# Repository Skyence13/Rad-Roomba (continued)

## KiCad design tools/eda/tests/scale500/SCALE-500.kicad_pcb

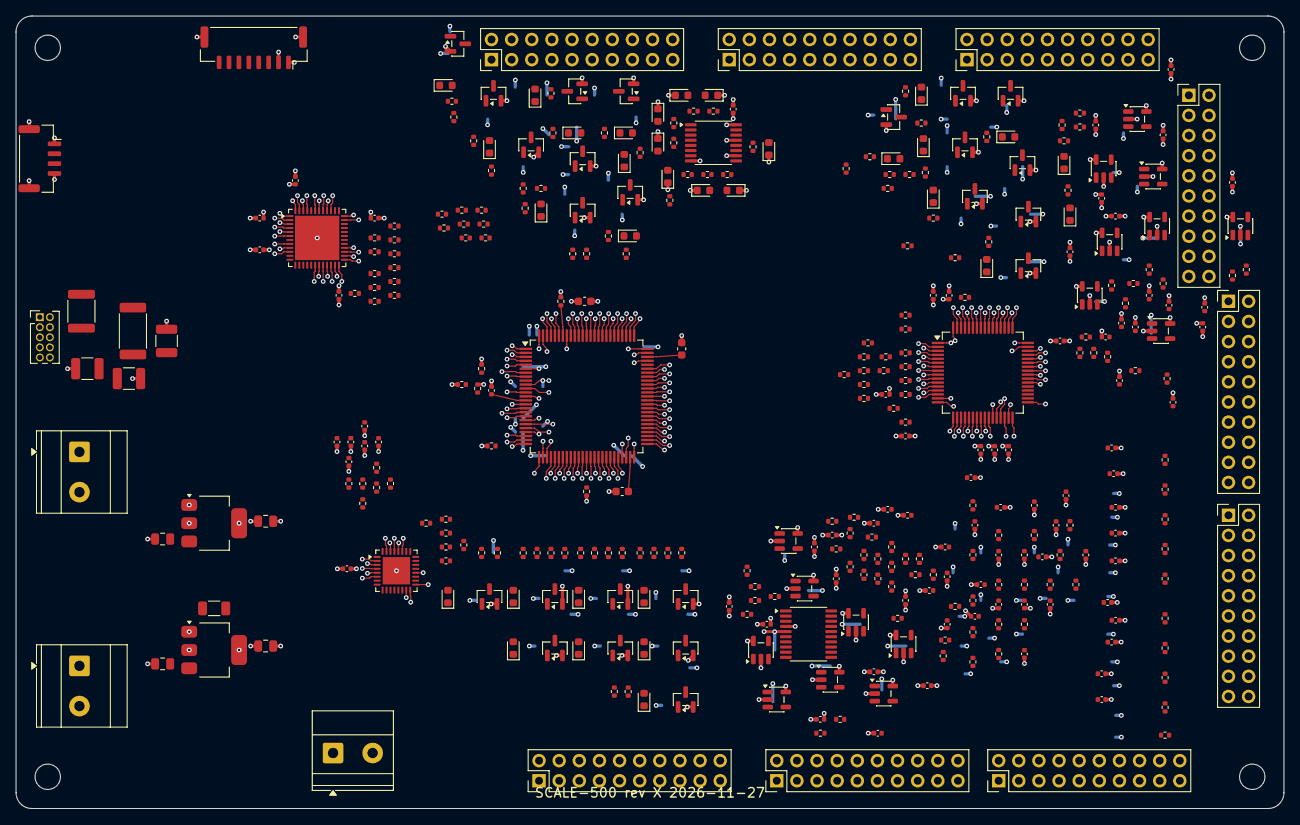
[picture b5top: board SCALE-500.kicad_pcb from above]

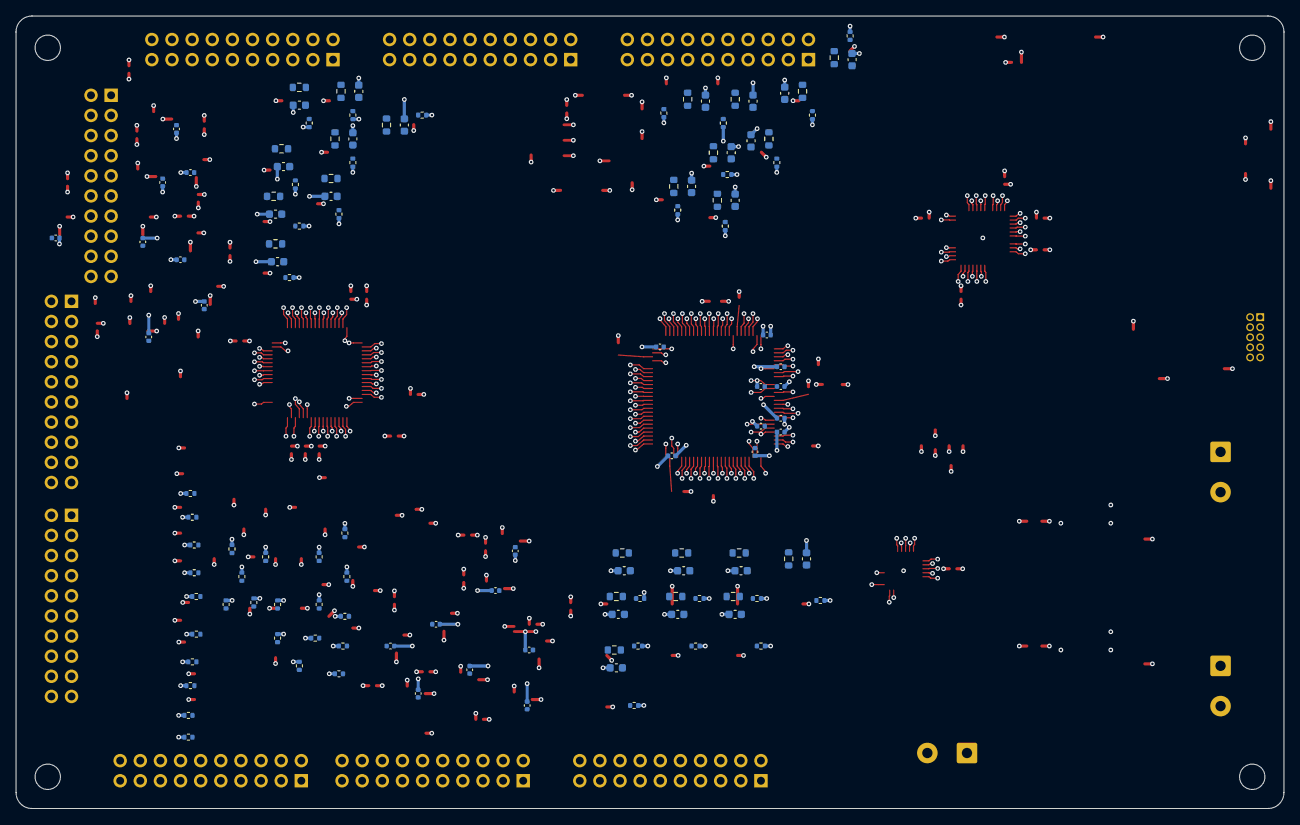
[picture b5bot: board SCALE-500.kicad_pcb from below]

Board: 6 copper layers, 160.0 x 100.0 mm, 497 parts (124 on the bottom side), 393 nets.

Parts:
C1, C2, C3: 22u; C_1210_3225Metric
C4, C6: 10u; C_0805_2012Metric
C5, C7: 22u; C_0805_2012Metric
C10, C11, C12, C13, C14, C15, C16, C17, C18, C19, C22, C30, C31, C32, C33, C34, C35, C36, C37, C40, C41, C42, C43, C44, C46, C47, C500, C501, C502, C503, C504, C505, C506, C507, C508, C509, C510, C511, C512, C513, C514, C515: 100n; C_0402_1005Metric
C20, C21: 2u2; C_0603_1608Metric
C23: 4u7; C_0603_1608Metric
C45: 1u; C_0402_1005Metric
C400, C401, C402, C403, C404, C405, C406, C407, C408, C409, C410, C411, C412, C413, C414, C415, C880, C881, C882, C883, C884, C885, C886, C887, C888, C889: 1n; C_0402_1005Metric
C600, C601, C602, C603, C604, C605, C606, C607, C608, C609, C610, C611, C612, C613, C614, C615: 100p; C_0402_1005Metric
C700, C701, C702, C703, C704, C705, C706, C707, C708, C709, C710, C711, C712, C713, C714, C715: 10n; C_0402_1005Metric
C860, C861, C862, C863, C864, C865: 47p; C_0402_1005Metric
C900, C901, C902, C903, C904, C905, C906, C907, C908, C909, C910, C911, C912, C913, C914, C915, C916, C917, C918, C919, C920, C921, C922, C923: 1n; C_0603_1608Metric
D200, D201, D202, D203, D204, D205, D206, D207: green; LED_0603_1608Metric
D300, D301, D302, D303, D304, D305, D306, D307, D308, D309, D310, D311, D312, D313, D314, D315, D316, D317, D318, D319, D320, D321, D322, D323: red; LED_0603_1608Metric
F1: 10A; Fuse_1812_4532Metric
H1, H2, H3, H4: M-hole 3.2mm; MountingHole_3.2mm_NPTH
J1: VBAT IN; TerminalBlock_Phoenix_MKDS-3-2-5.08_1x02_P5.08mm_Horizontal
J2: VBAT OUT A; TerminalBlock_Phoenix_MKDS-3-2-5.08_1x02_P5.08mm_Horizontal
J3: 12V IN; TerminalBlock_Phoenix_MKDS-1,5-2_1x02_P5.00mm_Horizontal
J10: OUT0; PinHeader_2x10_P2.54mm_Vertical
J11: OUT1; PinHeader_2x10_P2.54mm_Vertical
J12: OUT2; PinHeader_2x10_P2.54mm_Vertical
J20: AOUT0; PinHeader_2x10_P2.54mm_Vertical
J21: AOUT1; PinHeader_2x10_P2.54mm_Vertical
J30: AIN0; PinHeader_2x10_P2.54mm_Vertical
J31: AIN1; PinHeader_2x10_P2.54mm_Vertical
J32: DIN; PinHeader_2x10_P2.54mm_Vertical
J40: SWD; PinHeader_2x05_P1.27mm_Vertical
J41: GH8; JST_GH_SM08B-GHS-TB_1x08-1MP_P1.25mm_Horizontal
J42: GH4; JST_GH_SM04B-GHS-TB_1x04-1MP_P1.25mm_Horizontal
J43: EXP; PinHeader_2x10_P2.54mm_Vertical
Q300, Q301, Q302, Q303, Q304, Q305, Q306, Q307, Q308, Q309, Q310, Q311, Q312, Q313, Q314, Q315, Q316, Q317, Q318, Q319, Q320, Q321, Q322, Q323: AO3400A; SOT-23
R1: 0R; R_1206_3216Metric
R10, R11, R700, R701, R702, R703, R704, R705, R706, R707, R708, R709, R710, R711, R712, R713, R714, R715: 10k; R_0402_1005Metric
R12, R13, R14, R15: 4k7; R_0402_1005Metric
R100, R101, R102, R103, R104, R105, R106, R107, R108, R109, R110, R111, R112, R113, R114, R115, R800, R801, R802, R803, R804, R805, R806, R807, R808, R809, R810, R811, R820, R821, R822, R823, R824, R825, R830, R831, R832, R833, R840, R841, R842, R843, R844, R845, R846, R847, R850, R851, R852, R853, R854, R855, R856, R857, R860, R861, R862, R863, R864, R865: 33R; R_0402_1005Metric
R200, R201, R202, R203, R204, R205, R206, R207, R400, R401, R402, R403, R404, R405, R406, R407, R408, R409, R410, R411, R412, R413, R414, R415, R870, R871, R872, R873, R874, R875, R876, R877, R878, R879: 1k; R_0402_1005Metric
R300, R301, R302, R303, R304, R305, R306, R307, R308, R309, R310, R311, R312, R313, R314, R315, R316, R317, R318, R319, R320, R321, R322, R323, R500, R501, R502, R503, R504, R505, R506, R507, R508, R509, R510, R511, R512, R513, R514, R515: 100R; R_0402_1005Metric
R330, R331, R332, R333, R334, R335, R336, R337, R338, R339, R340, R341, R342, R343, R344, R345, R346, R347, R348, R349, R350, R351, R352, R353, R730, R731, R732, R733, R734, R735, R736, R737, R738, R739, R740, R741, R742, R743, R744, R745, R880, R881, R882, R883, R884, R885, R886, R887, R888, R889: 100k; R_0402_1005Metric
R360, R361, R362, R363, R364, R365, R366, R367, R368, R369, R370, R371, R372, R373, R374, R375, R376, R377, R378, R379, R380, R381, R382, R383: 2k2; R_0402_1005Metric
R900, R901, R902, R903, R904, R905, R906, R907, R908, R909, R910, R911, R912, R913, R914, R915, R916, R917, R918, R919, R920, R921, R922, R923: 47R; R_0603_1608Metric
RS1: 2m; R_2512_6332Metric
U1: STM32F407VET6; LQFP-100_14x14mm_P0.5mm
U2: STM32G474RET6; LQFP-64_10x10mm_P0.5mm
U3: STM32F103CBU6; QFN-48-1EP_7x7mm_P0.5mm_EP5.6x5.6mm
U4: STM32G031K8U6; QFN-32-1EP_5x5mm_P0.5mm_EP3.45x3.45mm
U5: STM32G031F8P6; TSSOP-20_4.4x6.5mm_P0.65mm
U6: 74HC595; TSSOP-16_4.4x5mm_P0.65mm
U7: AMS1117-5.0; SOT-223-3_TabPin2
U8: AMS1117-3.3; SOT-223-3_TabPin2
U400, U401, U402, U403, U404, U405, U406, U407, U408, U409, U410, U411, U412, U413, U414, U415: MCP6001; SOT-23-5

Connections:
+3V3: C7.1, C10.1, C11.1, C12.1, C13.1, C14.1, C15.1, C16.1, C17.1, C18.1, C19.1, C23.1, C30.1, C31.1, C32.1, C33.1, C34.1, C35.1, C36.1, C37.1, C40.1, C41.1, C42.1, C43.1, C44.1, C45.1, C46.1, C47.1, C500.1, C501.1, C502.1, C503.1, C504.1, C505.1, C506.1, C507.1, C508.1, C509.1, C510.1, C511.1, C512.1, C513.1, C514.1, C515.1, J20.19, J21.19, J40.1, J41.1, J42.1, J43.19, R10.1, R12.1, R13.1, R14.1, R15.1, U1.6, U1.11, U1.19, U1.21, U1.22, U1.28, U1.50, U1.75, U1.100, U2.1, U2.16, U2.28, U2.29, U2.32, U2.48, U2.64, U3.1, U3.9, U3.24, U3.36, U3.48, U4.4, U5.4, U6.10, U6.16, U8.2, U400.5, U401.5, U402.5, U403.5, U404.5, U405.5, U406.5, U407.5, U408.5, U409.5, U410.5, U411.5, U412.5, U413.5, U414.5, U415.5
+5V: C5.1, C6.1, J20.20, J21.20, J43.20, U7.2, U8.3
+12V: C4.1, J3.1, J10.2, J10.4, J10.6, J10.8, J10.10, J10.12, J10.14, J10.16, J11.2, J11.4, J11.6, J11.8, J11.10, J11.12, J11.14, J11.16, J12.2, J12.4, J12.6, J12.8, J12.10, J12.12, J12.14, J12.16, R1.1, U7.3
AIN00: C700.1, R700.2, U2.54
AIN01: C701.1, R701.2, U2.2
AIN02: C702.1, R702.2, U2.3
AIN03: C703.1, R703.2, U2.4
AIN04: C704.1, R704.2, U2.12
AIN05: C705.1, R705.2, U2.13
AIN06: C706.1, R706.2, U2.14
AIN07: C707.1, R707.2, U2.17
AIN08: C708.1, R708.2, U2.18
AIN09: C709.1, R709.2, U2.19
AIN10: C710.1, R710.2, U2.20
AIN11: C711.1, R711.2, U2.21
AIN12: C712.1, R712.2, U2.42
AIN13: C713.1, R713.2, U2.43
AIN14: C714.1, R714.2, U2.44
AIN15: C715.1, R715.2, U2.45
AIN_X00: J30.1, R700.1, R730.1
AIN_X01: J30.2, R701.1, R731.1
AIN_X02: J30.3, R702.1, R732.1
AIN_X03: J30.4, R703.1, R733.1
AIN_X04: J30.5, R704.1, R734.1
AIN_X05: J30.6, R705.1, R735.1
AIN_X06: J30.7, R706.1, R736.1
AIN_X07: J30.8, R707.1, R737.1
AIN_X08: J31.1, R708.1, R738.1
AIN_X09: J31.2, R709.1, R739.1
AIN_X10: J31.3, R710.1, R740.1
AIN_X11: J31.4, R711.1, R741.1
AIN_X12: J31.5, R712.1, R742.1
AIN_X13: J31.6, R713.1, R743.1
AIN_X14: J31.7, R714.1, R744.1
AIN_X15: J31.8, R715.1, R745.1
AO00: C600.1, J20.1, R500.2
AO01: C601.1, J20.3, R501.2
AO02: C602.1, J20.5, R502.2
AO03: C603.1, J20.7, R503.2
AO04: C604.1, J20.9, R504.2
AO05: C605.1, J20.11, R505.2
AO06: C606.1, J20.13, R506.2
AO07: C607.1, J20.15, R507.2
AO08: C608.1, J21.1, R508.2
AO09: C609.1, J21.3, R509.2
AO10: C610.1, J21.5, R510.2
AO11: C611.1, J21.7, R511.2
AO12: C612.1, J21.9, R512.2
AO13: C613.1, J21.11, R513.2
AO14: C614.1, J21.13, R514.2
AO15: C615.1, J21.15, R515.2
AUXH00: R840.1, U3.43
AUXH01: R841.1, U3.45
AUXH02: R842.1, U3.46
AUXH03: R843.1, U3.21
AUXH04: R844.1, U3.22
AUXH05: R845.1, U3.25
AUXH06: R846.1, U3.26
AUXH07: R847.1, U3.27
AUXHC00: J43.1, R840.2
AUXHC01: J43.2, R841.2
AUXHC02: J43.3, R842.2
AUXHC03: J43.4, R843.2
AUXHC04: J43.5, R844.2
AUXHC05: J43.6, R845.2
AUXHC06: J43.7, R846.2
AUXHC07: J43.8, R847.2
AUXT00: R850.1, U5.2
AUXT01: R851.1, U5.7
AUXT02: R852.1, U5.8
AUXT03: R853.1, U5.9
AUXT04: R854.1, U5.10
AUXT05: R855.1, U5.11
AUXT06: R856.1, U5.12
AUXT07: R857.1, U5.13
AUXTC00: J43.9, R850.2
AUXTC01: J43.10, R851.2
AUXTC02: J43.11, R852.2
AUXTC03: J43.12, R853.2
AUXTC04: J43.13, R854.2
AUXTC05: J43.14, R855.2
AUXTC06: J43.15, R856.2
AUXTC07: J43.16, R857.2
B2R_00: R100.2, U2.7
B2R_01: R101.2, U2.5
B2R_02: R102.2, U2.6
B2R_03: R103.2, U2.55
B2R_04: R104.2, U2.8
B2R_05: R105.2, U2.9
B2R_06: R106.2, U2.10
B2R_07: R107.2, U2.11
B2R_08: R108.2, U2.22
B2R_09: R109.2, U2.23
B2R_10: R110.2, U2.38
B2R_11: R111.2, U2.39
B2R_12: R112.2, U2.40
B2R_13: R113.2, U2.41
B2R_14: R114.2, U2.52
B2R_15: R115.2, U2.53
B2_00: R100.1, U1.12
B2_01: R101.1, U1.13
B2_02: R102.1, U1.97
B2_03: R103.1, U1.98
B2_04: R104.1, U1.1
B2_05: R105.1, U1.2
B2_06: R106.1, U1.3
B2_07: R107.1, U1.4
B2_08: R108.1, U1.5
B2_09: R109.1, U1.38
B2_10: R110.1, U1.39
B2_11: R111.1, U1.40
B2_12: R112.1, U1.41
B2_13: R113.1, U1.42
B2_14: R114.1, U1.43
B2_15: R115.1, U1.44
B3R_00: R800.2, U3.5
B3R_01: R801.2, U3.6
B3R_02: R802.2, U3.2
B3R_03: R803.2, U3.3
B3R_04: R804.2, U3.4
B3R_05: R805.2, U3.18
B3R_06: R806.2, U3.19
B3R_07: R807.2, U3.20
B3R_08: R808.2, U3.39
B3R_09: R809.2, U3.40
B3R_10: R810.2, U3.41
B3R_11: R811.2, U3.42
B3_00: R800.1, U1.45
B3_01: R801.1, U1.46
B3_02: R802.1, U1.81
B3_03: R803.1, U1.82
B3_04: R804.1, U1.83
B3_05: R805.1, U1.84
B3_06: R806.1, U1.85
B3_07: R807.1, U1.86
B3_08: R808.1, U1.87
B3_09: R809.1, U1.88
B3_10: R810.1, U1.55
B3_11: R811.1, U1.56
B4R_00: R820.2, U4.6
B4R_01: R821.2, U4.20
B4R_02: R822.2, U4.2
B4R_03: R823.2, U4.3
B4R_04: R824.2, U4.15
B4R_05: R825.2, U4.16
B4_00: R820.1, U1.57
B4_01: R821.1, U1.58
B4_02: R822.1, U1.59
B4_03: R823.1, U1.60
B4_04: R824.1, U1.61
B4_05: R825.1, U1.62
B5R_00: R830.2, U5.6
B5R_01: R831.2, U5.3
B5R_02: R832.2, U5.20
B5R_03: R833.2, U5.1
B5_00: R830.1, U1.23
B5_01: R831.1, U1.24
B5_02: R832.1, U1.25
B5_03: R833.1, U1.26
BOOT0: R11.1, U1.94
DIN00: C880.1, R870.2, U1.34
DIN01: C881.1, R871.2, U1.63
DIN02: C882.1, R872.2, U1.64
DIN03: C883.1, R873.2, U1.65
DIN04: C884.1, R874.2, U1.66
DIN05: C885.1, R875.2, U1.78
DIN06: C886.1, R876.2, U1.79
DIN07: C887.1, R877.2, U1.80
DIN08: C888.1, R878.2, U1.7
DIN09: C889.1, R879.2, U1.8
DIN_X00: J32.1, R870.1, R880.1
DIN_X01: J32.2, R871.1, R881.1
DIN_X02: J32.3, R872.1, R882.1
DIN_X03: J32.4, R873.1, R883.1
DIN_X04: J32.5, R874.1, R884.1
DIN_X05: J32.6, R875.1, R885.1
DIN_X06: J32.7, R876.1, R886.1
DIN_X07: J32.8, R877.1, R887.1
DIN_X08: J32.9, R878.1, R888.1
DIN_X09: J32.10, R879.1, R889.1
FET_IN00: R300.1, U1.32
FET_IN01: R301.1, U1.67
FET_IN02: R302.1, U1.68
FET_IN03: R303.1, U1.69
FET_IN04: R304.1, U1.70
FET_IN05: R305.1, U1.71
FET_IN06: R306.1, U1.72
FET_IN07: R307.1, U1.76
FET_IN08: R308.1, U1.77
FET_IN09: R309.1, U1.35
FET_IN10: R310.1, U1.36
FET_IN11: R311.1, U1.37
FET_IN12: R312.1, U1.89
FET_IN13: R313.1, U1.90
FET_IN14: R314.1, U1.91
FET_IN15: R315.1, U1.92
FET_IN16: R316.1, U1.93
FET_IN17: R317.1, U1.95
FET_IN18: R318.1, U1.96
FET_IN19: R319.1, U1.47
FET_IN20: R320.1, U1.48
FET_IN21: R321.1, U1.51
FET_IN22: R322.1, U1.52
FET_IN23: R323.1, U1.53
G00: Q300.1, R300.2, R330.1
G01: Q301.1, R301.2, R331.1
G02: Q302.1, R302.2, R332.1
G03: Q303.1, R303.2, R333.1
G04: Q304.1, R304.2, R334.1
G05: Q305.1, R305.2, R335.1
G06: Q306.1, R306.2, R336.1
G07: Q307.1, R307.2, R337.1
G08: Q308.1, R308.2, R338.1
G09: Q309.1, R309.2, R339.1
G10: Q310.1, R310.2, R340.1
G11: Q311.1, R311.2, R341.1
G12: Q312.1, R312.2, R342.1
G13: Q313.1, R313.2, R343.1
G14: Q314.1, R314.2, R344.1
G15: Q315.1, R315.2, R345.1
G16: Q316.1, R316.2, R346.1
G17: Q317.1, R317.2, R347.1
G18: Q318.1, R318.2, R348.1
G19: Q319.1, R319.2, R349.1
G20: Q320.1, R320.2, R350.1
G21: Q321.1, R321.2, R351.1
G22: Q322.1, R322.2, R352.1
G23: Q323.1, R323.2, R353.1
GH0: R860.1, U4.17
GH1: R861.1, U4.27
GH2: R862.1, U4.28
GH3: R863.1, U4.29
GH4: R864.1, U4.30
GH5: R865.1, U4.31
GHC0: C860.1, J41.3, R860.2
GHC1: C861.1, J41.4, R861.2
GHC2: C862.1, J41.5, R862.2
GHC3: C863.1, J41.6, R863.2
GHC4: C864.1, J41.7, R864.2
GHC5: C865.1, J41.8, R865.2
GND: C1.2, C2.2, C3.2, C4.2, C5.2, C6.2, C7.2, C10.2, C11.2, C12.2, C13.2, C14.2, C15.2, C16.2, C17.2, C18.2, C19.2, C20.2, C21.2, C22.2, C23.2, C30.2, C31.2, C32.2, C33.2, C34.2, C35.2, C36.2, C37.2, C40.2, C41.2, C42.2, C43.2, C44.2, C45.2, C46.2, C47.2, C400.2, C401.2, C402.2, C403.2, C404.2, C405.2, C406.2, C407.2, C408.2, C409.2, C410.2, C411.2, C412.2, C413.2, C414.2, C415.2, C500.2, C501.2, C502.2, C503.2, C504.2, C505.2, C506.2, C507.2, C508.2, C509.2, C510.2, C511.2, C512.2, C513.2, C514.2, C515.2, C600.2, C601.2, C602.2, C603.2, C604.2, C605.2, C606.2, C607.2, C608.2, C609.2, C610.2, C611.2, C612.2, C613.2, C614.2, C615.2, C700.2, C701.2, C702.2, C703.2, C704.2, C705.2, C706.2, C707.2, C708.2, C709.2, C710.2, C711.2, C712.2, C713.2, C714.2, C715.2, C860.2, C861.2, C862.2, C863.2, C864.2, C865.2, C880.2, C881.2, C882.2, C883.2, C884.2, C885.2, C886.2, C887.2, C888.2, C889.2, C900.2, C901.2, C902.2, C903.2, C904.2, C905.2, C906.2, C907.2, C908.2, C909.2, C910.2, C911.2, C912.2, C913.2, C914.2, C915.2, C916.2, C917.2, C918.2, C919.2, C920.2, C921.2, C922.2, C923.2, D200.1, D201.1, D202.1, D203.1, D204.1, D205.1, D206.1, D207.1, J1.2, J2.2, J3.2, J10.17, J10.18, J10.19, J10.20, J11.17, J11.18, J11.19, J11.20, J12.17, J12.18, J12.19, J12.20, J20.2, J20.4, J20.6, J20.8, J20.10, J20.12, J20.14, J20.16, J20.17, J20.18, J21.2, J21.4, J21.6, J21.8, J21.10, J21.12, J21.14, J21.16, J21.17, J21.18, J30.9, J30.10, J30.11, J30.12, J30.13, J30.14, J30.15, J30.16, J30.17, J30.18, J30.19, J30.20, J31.9, J31.10, J31.11, J31.12, J31.13, J31.14, J31.15, J31.16, J31.17, J31.18, J31.19, J31.20, J32.11, J32.12, J32.13, J32.14, J32.15, J32.16, J32.17, J32.18, J32.19, J32.20, J40.3, J40.5, J40.7, J40.9, J41.2, J41.MP, J42.4, J42.MP, J43.17, J43.18, Q300.2, Q301.2, Q302.2, Q303.2, Q304.2, Q305.2, Q306.2, Q307.2, Q308.2, Q309.2, Q310.2, Q311.2, Q312.2, Q313.2, Q314.2, Q315.2, Q316.2, Q317.2, Q318.2, Q319.2, Q320.2, Q321.2, Q322.2, Q323.2, R11.2, R330.2, R331.2, R332.2, R333.2, R334.2, R335.2, R336.2, R337.2, R338.2, R339.2, R340.2, R341.2, R342.2, R343.2, R344.2, R345.2, R346.2, R347.2, R348.2, R349.2, R350.2, R351.2, R352.2, R353.2, R730.2, R731.2, R732.2, R733.2, R734.2, R735.2, R736.2, R737.2, R738.2, R739.2, R740.2, R741.2, R742.2, R743.2, R744.2, R745.2, R880.2, R881.2, R882.2, R883.2, R884.2, R885.2, R886.2, R887.2, R888.2, R889.2, U1.10, U1.20, U1.27, U1.74, U1.99, U2.15, U2.27, U2.31, U2.47, U2.63, U3.8, U3.23, U3.35, U3.47, U3.49, U4.5, U4.33, U5.5, U6.8, U6.13, U7.1, U8.1, U400.2, U401.2, U402.2, U403.2, U404.2, U405.2, U406.2, U407.2, U408.2, U409.2, U410.2, U411.2, U412.2, U413.2, U414.2, U415.2
I2C_SCL: J42.2, R12.2, U1.16, U3.28
I2C_SDA: J42.3, R13.2, U1.17, U3.10
LK00: D300.1, R360.1
LK01: D301.1, R361.1
LK02: D302.1, R362.1
LK03: D303.1, R363.1
LK04: D304.1, R364.1
LK05: D305.1, R365.1
LK06: D306.1, R366.1
LK07: D307.1, R367.1
LK08: D308.1, R368.1
LK09: D309.1, R369.1
LK10: D310.1, R370.1
LK11: D311.1, R371.1
LK12: D312.1, R372.1
LK13: D313.1, R373.1
LK14: D314.1, R374.1
LK15: D315.1, R375.1
LK16: D316.1, R376.1
LK17: D317.1, R377.1
LK18: D318.1, R378.1
LK19: D319.1, R379.1
LK20: D320.1, R380.1
LK21: D321.1, R381.1
LK22: D322.1, R382.1
LK23: D323.1, R383.1
NRST: C22.1, J40.6, R10.2, U1.14
OPB00: C400.1, R400.2, U400.3
OPB01: C401.1, R401.2, U401.3
OPB02: C402.1, R402.2, U402.3
OPB03: C403.1, R403.2, U403.3
OPB04: C404.1, R404.2, U404.3
OPB05: C405.1, R405.2, U405.3
OPB06: C406.1, R406.2, U406.3
OPB07: C407.1, R407.2, U407.3
OPB08: C408.1, R408.2, U408.3
OPB09: C409.1, R409.2, U409.3
OPB10: C410.1, R410.2, U410.3
OPB11: C411.1, R411.2, U411.3
OPB12: C412.1, R412.2, U412.3
OPB13: C413.1, R413.2, U413.3
OPB14: C414.1, R414.2, U414.3
OPB15: C415.1, R415.2, U415.3
OPIN00: R400.1, U2.46
OPIN01: R401.1, U2.49
OPIN02: R402.1, U2.50
OPIN03: R403.1, U2.51
OPIN04: R404.1, U2.24
OPIN05: R405.1, U2.25
OPIN06: R406.1, U2.26
OPIN07: R407.1, U2.56
OPIN08: R408.1, U2.57
OPIN09: R409.1, U2.58
OPIN10: R410.1, U2.59
OPIN11: R411.1, U2.60
OPIN12: R412.1, U2.61
OPIN13: R413.1, U2.62
OPIN14: R414.1, U2.30
OPIN15: R415.1, U2.33
OPO00: R500.1, U400.1, U400.4
OPO01: R501.1, U401.1, U401.4
OPO02: R502.1, U402.1, U402.4
OPO03: R503.1, U403.1, U403.4
OPO04: R504.1, U404.1, U404.4
OPO05: R505.1, U405.1, U405.4
OPO06: R506.1, U406.1, U406.4
OPO07: R507.1, U407.1, U407.4
OPO08: R508.1, U408.1, U408.4
OPO09: R509.1, U409.1, U409.4
OPO10: R510.1, U410.1, U410.4
OPO11: R511.1, U411.1, U411.4
OPO12: R512.1, U412.1, U412.4
OPO13: R513.1, U413.1, U413.4
OPO14: R514.1, U414.1, U414.4
OPO15: R515.1, U415.1, U415.4
SN00: C900.1, R900.2
SN01: C901.1, R901.2
SN02: C902.1, R902.2
SN03: C903.1, R903.2
SN04: C904.1, R904.2
SN05: C905.1, R905.2
SN06: C906.1, R906.2
SN07: C907.1, R907.2
SN08: C908.1, R908.2
SN09: C909.1, R909.2
SN10: C910.1, R910.2
SN11: C911.1, R911.2
SN12: C912.1, R912.2
SN13: C913.1, R913.2
SN14: C914.1, R914.2
SN15: C915.1, R915.2
SN16: C916.1, R916.2
SN17: C917.1, R917.2
SN18: C918.1, R918.2
SN19: C919.1, R919.2
SN20: C920.1, R920.2
SN21: C921.1, R921.2
SN22: C922.1, R922.2
SN23: C923.1, R923.2
SRL0: D200.2, R200.2
SRL1: D201.2, R201.2
SRL2: D202.2, R202.2
SRL3: D203.2, R203.2
SRL4: D204.2, R204.2
SRL5: D205.2, R205.2
SRL6: D206.2, R206.2
SRL7: D207.2, R207.2
SRQ0: R200.1, U6.15
SRQ1: R201.1, U6.1
SRQ2: R202.1, U6.2
SRQ3: R203.1, U6.3
SRQ4: R204.1, U6.4
SRQ5: R205.1, U6.5
SRQ6: R206.1, U6.6
SRQ7: R207.1, U6.7
SR_CLK: U1.30, U6.11
SR_LAT: U1.31, U6.12
SR_SER: U1.29, U6.14
SW00: J10.1, Q300.3, R360.2, R900.1
SW01: J10.3, Q301.3, R361.2, R901.1
SW02: J10.5, Q302.3, R362.2, R902.1
SW03: J10.7, Q303.3, R363.2, R903.1
SW04: J10.9, Q304.3, R364.2, R904.1
SW05: J10.11, Q305.3, R365.2, R905.1
SW06: J10.13, Q306.3, R366.2, R906.1
SW07: J10.15, Q307.3, R367.2, R907.1
SW08: J11.1, Q308.3, R368.2, R908.1
SW09: J11.3, Q309.3, R369.2, R909.1
SW10: J11.5, Q310.3, R370.2, R910.1
SW11: J11.7, Q311.3, R371.2, R911.1
SW12: J11.9, Q312.3, R372.2, R912.1
SW13: J11.11, Q313.3, R373.2, R913.1
SW14: J11.13, Q314.3, R374.2, R914.1
SW15: J11.15, Q315.3, R375.2, R915.1
SW16: J12.1, Q316.3, R376.2, R916.1
SW17: J12.3, Q317.3, R377.2, R917.1
SW18: J12.5, Q318.3, R378.2, R918.1
SW19: J12.7, Q319.3, R379.2, R919.1
SW20: J12.9, Q320.3, R380.2, R920.1
SW21: J12.11, Q321.3, R381.2, R921.1
SW22: J12.13, Q322.3, R382.2, R922.1
SW23: J12.15, Q323.3, R383.2, R923.1
SWCLK: J40.4, U1.15
SWDIO: J40.2, R15.2, U1.54
UART_RX: J40.10, R14.2, U1.33
UART_TX: J40.8, U1.18
VBAT: F1.1, J1.1
VBAT_F: F1.2, RS1.1
VBAT_S: C1.1, C2.1, C3.1, J2.1, RS1.2
VCAP1: C20.1, U1.49
VCAP2: C21.1, U1.73
VLED: D300.2, D301.2, D302.2, D303.2, D304.2, D305.2, D306.2, D307.2, D308.2, D309.2, D310.2, D311.2, D312.2, D313.2, D314.2, D315.2, D316.2, D317.2, D318.2, D319.2, D320.2, D321.2, D322.2, D323.2, R1.2

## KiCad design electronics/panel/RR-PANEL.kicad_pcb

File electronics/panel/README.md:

# RR-PANEL rev A — annunciator panel (stage 2, KiCad 9)

| | |
|---|---|
| Netlist source | `design/circuit.py` (stage 1, reviewed baseline — not edited) |
| Board definition | `board.py` (the only hand-edited file; everything else is generated) |
| Board | 70 × 24 mm, 2 layers, 1.6 mm, 24 parts (19 fitted + 2 holes, 2 fiducials, 3 test pads), 15 nets |
| Result | **PASS** — ERC 0 errors / 0 warnings, DRC 0 errors / 0 warnings, 0 unconnected, schematic parity 0, netlist cross-check OK (24 components, 15 nets) |

## Commands

```
python3 electronics/panel/design/circuit.py                 # stage-1 self-check
python3 tools/eda/rrkicad.py build electronics/panel/board.py   # schematic, PCB, route (cached SES), ERC, DRC, all outputs (~25 s)
python3 tools/eda/rrkicad.py build electronics/panel/board.py --reroute   # force a fresh Freerouting run (~15 s routing)
python3 tools/eda/rrkicad.py check electronics/panel/board.py   # re-run ERC/DRC on the existing files
```

Outputs (`out/`): `RR-PANEL-schematic.pdf`, `gerber/` (Gerbers, PTH/NPTH Excellon, drill maps, job file),
`RR-PANEL-pos.csv`, `RR-PANEL-bom.csv`, `RR-PANEL-fab.pdf`, `RR-PANEL-assembly-top.pdf` / `-bottom.pdf`,
`RR-PANEL-copper.pdf`, `RR-PANEL.step`, `RR-PANEL-render-top.png` / `-bottom.png`, `pinmap.json`, `RR-PANEL.net`.
Reports: `reports/summary.json` (status, counts, BOM verify list), `reports/erc.*`, `reports/drc.*`,
`reports/import_report.json` (importer: 24 stock symbols, 0 local, 0 rejected hints, 0 missing footprints).
The routing result is `route/RR-PANEL.ses` + `route/route_meta.json` (keep under version control: the build re-uses it).

## Frame mapping

`circuit.py` / envelope board frame (u, v) → tool board frame (X, Y) = (u, v), no rotation, no offset.
Origin = lower-left corner seen from the top (component) side; X along the 70 mm axis in the LED order
READY (u 9) … FAULT (u 61); Y along the 24 mm axis. Pick-and-place, `pinmap.json`, the STEP model and
the drill origin use this frame. The board's orientation in the robot (`board_envelopes.yaml` RR-PANEL:
long axis along base y, component side up) does not say which end of u points to +y: **mechanical to
confirm** which edge the J1 cable leaves over (see below).

## What is tool-checked

ERC (0/0), DRC with schematic parity (0/0, 0 unconnected), pin-by-pin netlist cross-check of the generated
schematic against the definition (which is `circuit.py` imported 1:1), courtyards, edge clearance, hole
keep-outs (6 mm copper keep-out around H1/H2). **Not** checked by a tool: light-pipe alignment, the
mechanical fit in the shell, LED brightness, sounder level.

## Deviations from stage 1 (placement only — no net or part changes)

| # | What | Why |
|---|---|---|
| P1 | J1 and J2 are on the **top** side (stage 1: bottom side), at (30, 20.6) and (49.5, 20.6), mating face towards the v = 24 edge; the cable leaves over that long edge, not along the long axis | Envelope: bottom 3 mm max, GH side-entry header 4.25 mm. CCR-E08(d) offered "allow 4.5 mm or move them to the top"; no 4.5 mm allowance was granted (`board_envelopes.yaml` still says 3 mm), top allows 8 mm. A 10-pin GH (17 mm with pegs) cannot face a short edge: with H2's keep-out only 16 mm of the 24 mm edge is free. `harness/cables.md` W-023 / `harness/connectors.yaml` PNL.J1 still say "bottom side" — harness to update. |
| P2 | Holes, fiducials and test pads (`(pcb feature)` MPN) are excluded from the BOM | The stock footprints carry "exclude from BOM"; matching the symbol avoids a parity mismatch. They remain in the schematic and the PCB. |
| P3 | Silkscreen legend per LED (READY, MOVING, HOLD, CHARGE, FAULT) next to each LED on the top side | Assembly/service aid only. |

## Open items / UNVERIFIED

* `verify=True` from stage 1 (BOM notes): LED1–LED5 (Würth MPNs, intensity through the light pipe), BZ1 (Murata PKLCS1212E data recalled; sound level probably too low — fit the external sounder on J2).
* Mounting-hole positions (3.5, 20.5) / (66.5, 20.5) are the stage-1 proposal; mechanical gave none.
* Cable exit over the v = 24 edge (P1) and which board end faces +y in the robot: mechanical/harness to confirm.
* JST GH −25 °C rating (CCR-E05) unchanged.
* Only two top-side fiducials (as in `circuit.py`); the bottom side has no fiducials — acceptable for 0603/0805/SOD-123 and the 12 mm buzzer, add two if the assembler asks.

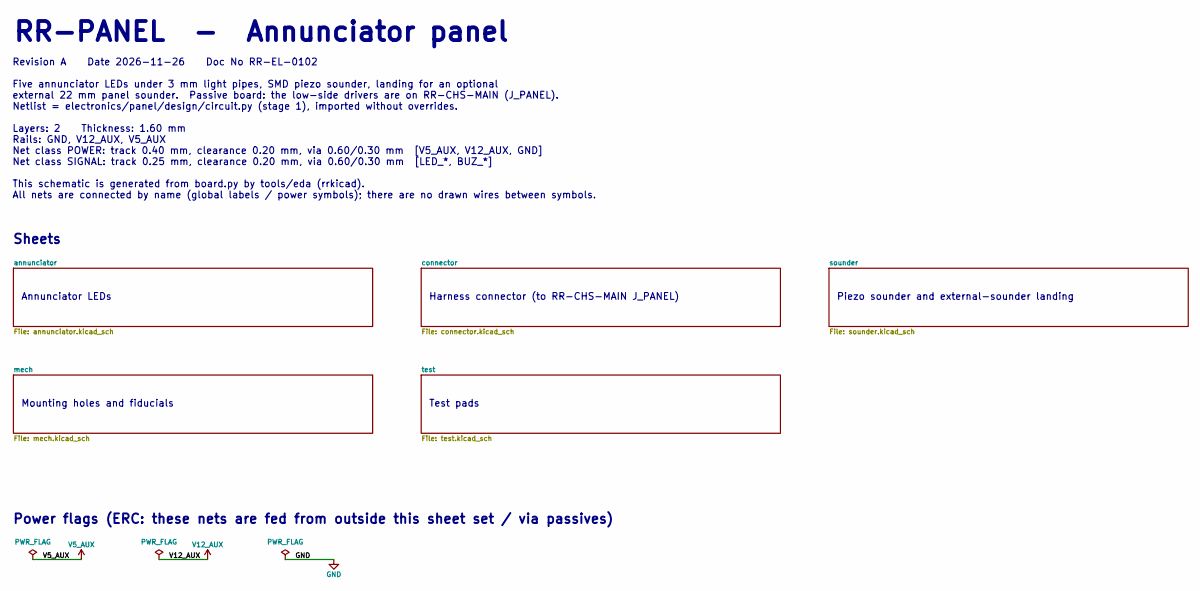
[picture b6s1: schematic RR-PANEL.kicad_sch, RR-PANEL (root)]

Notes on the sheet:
RR-PANEL - Annunciator panel
Revision A Date 2026-11-26 Doc No RR-EL-0102 Five annunciator LEDs under 3 mm light pipes, SMD piezo sounder, landing for an optional external 22 mm panel sounder. Passive board: the low-side drivers are on RR-CHS-MAIN (J_PANEL). Netlist = electronics/panel/design/circuit.py (stage 1), imported wit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
Sheets
Annunciator LEDs
Harness connector (to RR-CHS-MAIN J_PANEL)
Piezo sounder and external-sounder landing
Mounting holes and fiducials
Test pads
Power flags (ERC: these nets are fed from outside this sheet set / via passives)

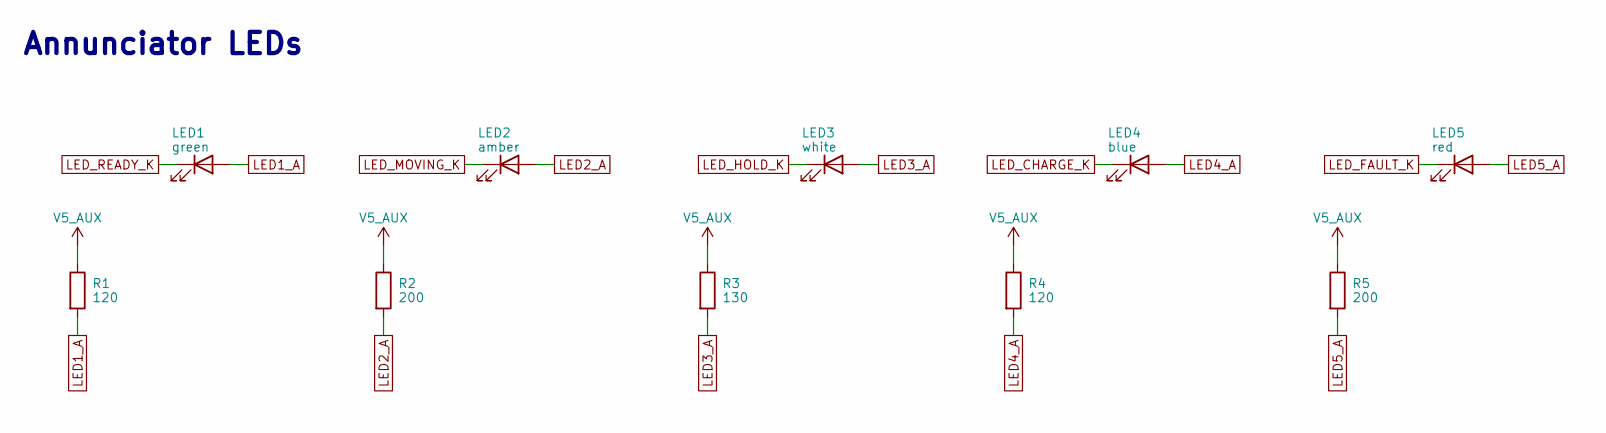
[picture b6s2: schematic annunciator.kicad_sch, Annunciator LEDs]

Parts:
LED1: green; LED_0805_2012Metric; MPN 150080GS75000
LED2: amber; LED_0805_2012Metric; MPN 150080YS75000
LED3: white; LED_0805_2012Metric; MPN 158080227A
LED4: blue; LED_0805_2012Metric; MPN 150080BS75000
LED5: red; LED_0805_2012Metric; MPN 150080RS75000
R1, R4: 120; R_0805_2012Metric; MPN RC0805FR-07120RL
R2, R5: 200; R_0805_2012Metric; MPN RC0805FR-07200RL
R3: 130; R_0805_2012Metric; MPN RC0805FR-07130RL

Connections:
LED1_A: LED1.2 (A), R1.2
LED2_A: LED2.2 (A), R2.2
LED3_A: LED3.2 (A), R3.2
LED4_A: LED4.2 (A), R4.2
LED5_A: LED5.2 (A), R5.2
LED_CHARGE_K: LED4.1 (K); also elsewhere on the board
LED_FAULT_K: LED5.1 (K); also elsewhere on the board
LED_HOLD_K: LED3.1 (K); also elsewhere on the board
LED_MOVING_K: LED2.1 (K); also elsewhere on the board
LED_READY_K: LED1.1 (K); also elsewhere on the board
V5_AUX: R1.1, R2.1, R3.1, R4.1, R5.1; also elsewhere on the board

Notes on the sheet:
Annunciator LEDs

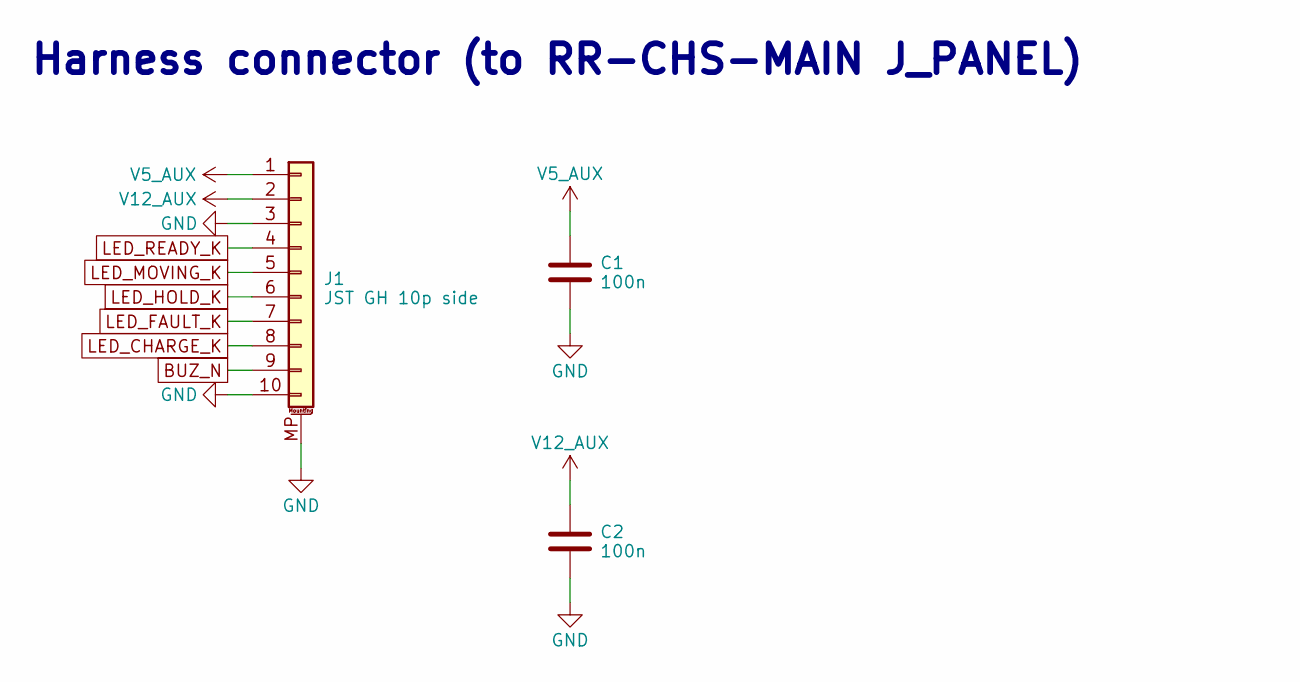
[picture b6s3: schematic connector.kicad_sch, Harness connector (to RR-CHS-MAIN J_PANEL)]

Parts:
C1, C2: 100n; C_0603_1608Metric; MPN CC0603KRX7R9BB104
J1: JST GH 10p side; JST_GH_SM10B-GHS-TB_1x10-1MP_P1.25mm_Horizontal; MPN SM10B-GHS-TB(LF)(SN)

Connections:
BUZ_N: J1.9; also elsewhere on the board
GND: C1.2, C2.2, J1.3, J1.10, J1.MP (MountPin); also elsewhere on the board
LED_CHARGE_K: J1.8; also elsewhere on the board
LED_FAULT_K: J1.7; also elsewhere on the board
LED_HOLD_K: J1.6; also elsewhere on the board
LED_MOVING_K: J1.5; also elsewhere on the board
LED_READY_K: J1.4; also elsewhere on the board
V5_AUX: C1.1, J1.1; also elsewhere on the board
V12_AUX: C2.1, J1.2; also elsewhere on the board

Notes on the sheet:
Harness connector (to RR-CHS-MAIN J_PANEL)

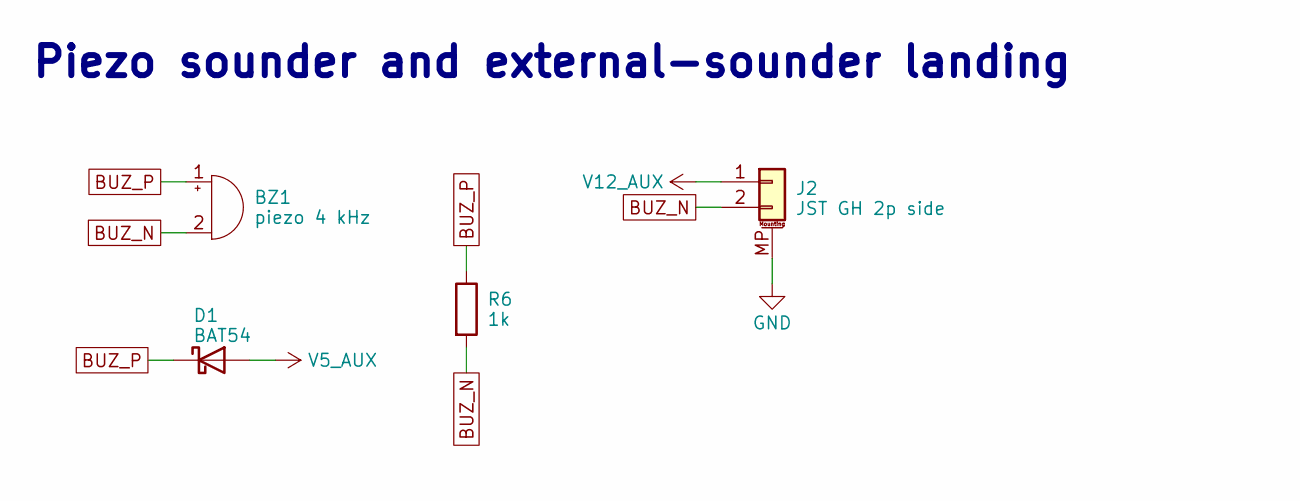
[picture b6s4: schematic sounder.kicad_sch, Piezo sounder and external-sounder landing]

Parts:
BZ1: piezo 4 kHz; Buzzer_Murata_PKLCS1212E; MPN PKLCS1212E4001-R1
D1: BAT54; D_SOD-123; MPN BAT54W-7-F
J2: JST GH 2p side; JST_GH_SM02B-GHS-TB_1x02-1MP_P1.25mm_Horizontal; MPN SM02B-GHS-TB(LF)(SN)
R6: 1k; R_0805_2012Metric; MPN RC0805FR-071KL

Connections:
BUZ_N: BZ1.2 (-), J2.2, R6.2; also elsewhere on the board
BUZ_P: BZ1.1 (+), D1.1 (K), R6.1
GND: J2.MP (MountPin); also elsewhere on the board
V5_AUX: D1.2 (A); also elsewhere on the board
V12_AUX: J2.1; also elsewhere on the board

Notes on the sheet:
Piezo sounder and external-sounder landing

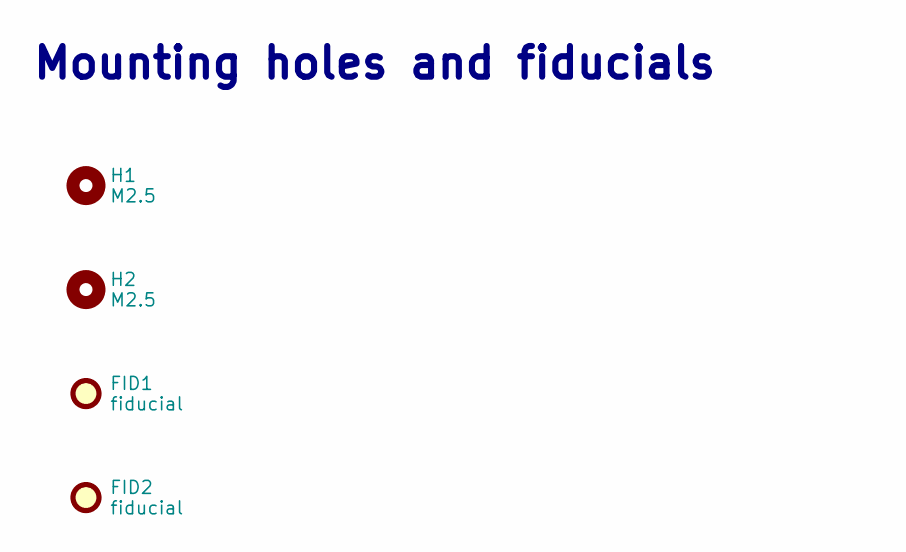
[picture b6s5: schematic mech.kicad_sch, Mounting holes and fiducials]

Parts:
FID1, FID2: fiducial; Fiducial_1mm_Mask2mm; MPN FIDUCIAL
H1, H2: M2.5; MountingHole_2.7mm_M2.5; MPN MOUNTING-HOLE-M2.5

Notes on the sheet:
Mounting holes and fiducials

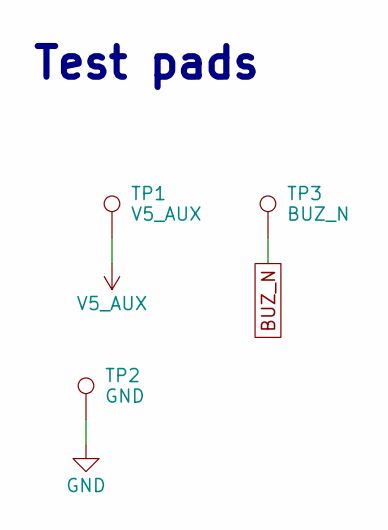
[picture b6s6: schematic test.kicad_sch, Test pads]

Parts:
TP1: V5_AUX; TestPoint_Pad_D1.5mm; MPN TP-PAD-1.5
TP2: GND; TestPoint_Pad_D1.5mm; MPN TP-PAD-1.5
TP3: BUZ_N; TestPoint_Pad_D1.5mm; MPN TP-PAD-1.5

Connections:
BUZ_N: TP3.1; also elsewhere on the board
GND: TP2.1; also elsewhere on the board
V5_AUX: TP1.1; also elsewhere on the board

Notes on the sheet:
Test pads

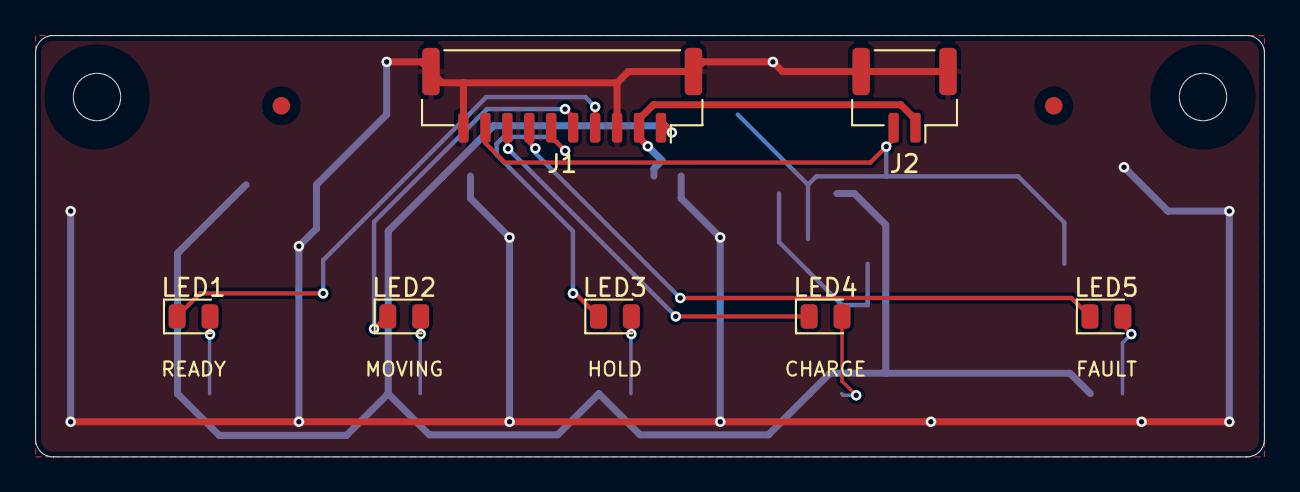
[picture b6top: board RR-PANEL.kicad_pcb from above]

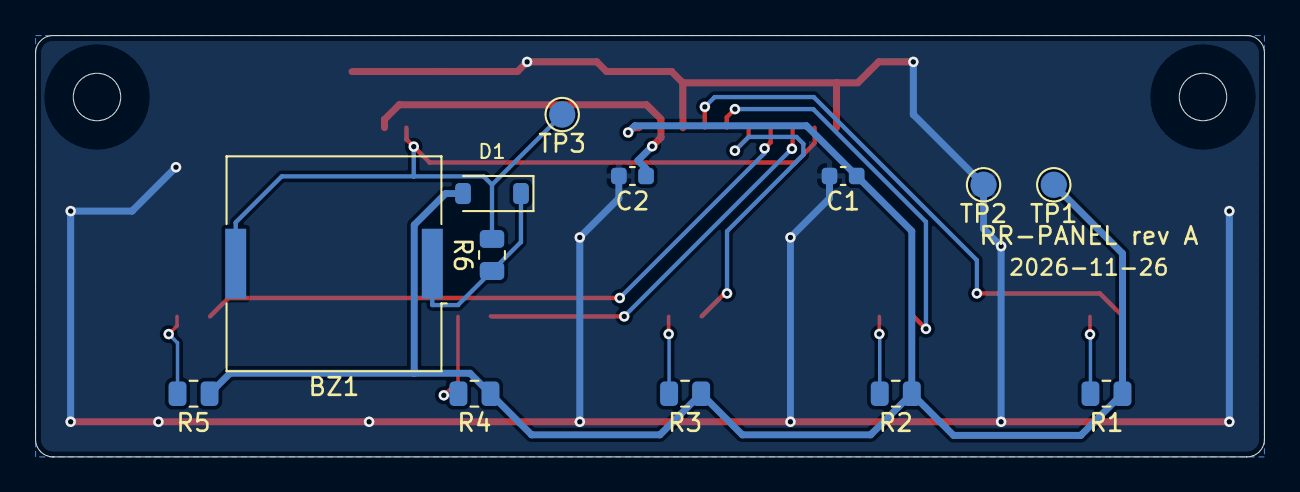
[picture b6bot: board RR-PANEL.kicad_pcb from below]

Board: 2 copper layers, 70.0 x 24.0 mm, 24 parts (13 on the bottom side), 15 nets.

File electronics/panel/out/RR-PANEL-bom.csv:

Refs,Qty,Value,Footprint,Manufacturer,MPN,DNP,Notes
BZ1,1,piezo 4 kHz,Buzzer_Beeper:Buzzer_Murata_PKLCS1212E,Murata,PKLCS1212E4001-R1,,"Recalled data [U]: >= 75 dB at 10 cm with 3 Vp-p, -40..+85 C. Driven single-ended 5 Vp-p at 4 kHz by the main-board FET (TIM5_CH1). Expected about 80 dB at 10 cm, i.e. about 60 dB at 1 m: NOT enough as a pre-motion alert in a noisy trailer. Fit the external sounder on J2 unless a sound-level test says otherwise.; verify: true"
C1 C2,2,100n,Capacitor_SMD:C_0603_1608Metric,Yageo,CC0603KRX7R9BB104,,
D1,1,BAT54,Diode_SMD:D_SOD-123,Diodes Inc.,BAT54W-7-F,,
J1,1,JST GH 10p side,Connector_JST:JST_GH_SM10B-GHS-TB_1x10-1MP_P1.25mm_Horizontal,JST,SM10B-GHS-TB(LF)(SN),,JST GH rated -25..+85 C [U]
J2,1,JST GH 2p side,Connector_JST:JST_GH_SM02B-GHS-TB_1x02-1MP_P1.25mm_Horizontal,JST,SM02B-GHS-TB(LF)(SN),,"Candidate: Schneider Harmony XB5KSB/XB5KS2 class buzzer [U part, level and temperature]. Requirement: >= 85 dB(A) at 30 cm, -25 C."
LED1,1,green,LED_SMD:LED_0805_2012Metric,Wurth Elektronik,150080GS75000,,I = (5.0 - 3.2) / 120 ohm = 15 mA [C]. Luminous intensity and daylight legibility through the light pipe are UNVERIFIED: test with the real pipe and bezel; resistor value is the adjustment.; verify: true
LED2,1,amber,LED_SMD:LED_0805_2012Metric,Wurth Elektronik,150080YS75000,,I = (5.0 - 2.0) / 200 ohm = 15 mA [C]. Luminous intensity and daylight legibility through the light pipe are UNVERIFIED: test with the real pipe and bezel; resistor value is the adjustment.; verify: true
LED3,1,white,LED_SMD:LED_0805_2012Metric,Wurth Elektronik,158080227A,,I = (5.0 - 3.0) / 130 ohm = 15 mA [C]. Luminous intensity and daylight legibility through the light pipe are UNVERIFIED: test with the real pipe and bezel; resistor value is the adjustment.; verify: true
LED4,1,blue,LED_SMD:LED_0805_2012Metric,Wurth Elektronik,150080BS75000,,I = (5.0 - 3.2) / 120 ohm = 15 mA [C]. Luminous intensity and daylight legibility through the light pipe are UNVERIFIED: test with the real pipe and bezel; resistor value is the adjustment.; verify: true
LED5,1,red,LED_SMD:LED_0805_2012Metric,Wurth Elektronik,150080RS75000,,I = (5.0 - 2.0) / 200 ohm = 15 mA [C]. Luminous intensity and daylight legibility through the light pipe are UNVERIFIED: test with the real pipe and bezel; resistor value is the adjustment.; verify: true
R1 R4,2,120,Resistor_SMD:R_0805_2012Metric,Yageo,RC0805FR-07120RL,,
R2 R5,2,200,Resistor_SMD:R_0805_2012Metric,Yageo,RC0805FR-07200RL,,
R3,1,130,Resistor_SMD:R_0805_2012Metric,Yageo,RC0805FR-07130RL,,
R6,1,1k,Resistor_SMD:R_0805_2012Metric,Yageo,RC0805FR-071KL,,
